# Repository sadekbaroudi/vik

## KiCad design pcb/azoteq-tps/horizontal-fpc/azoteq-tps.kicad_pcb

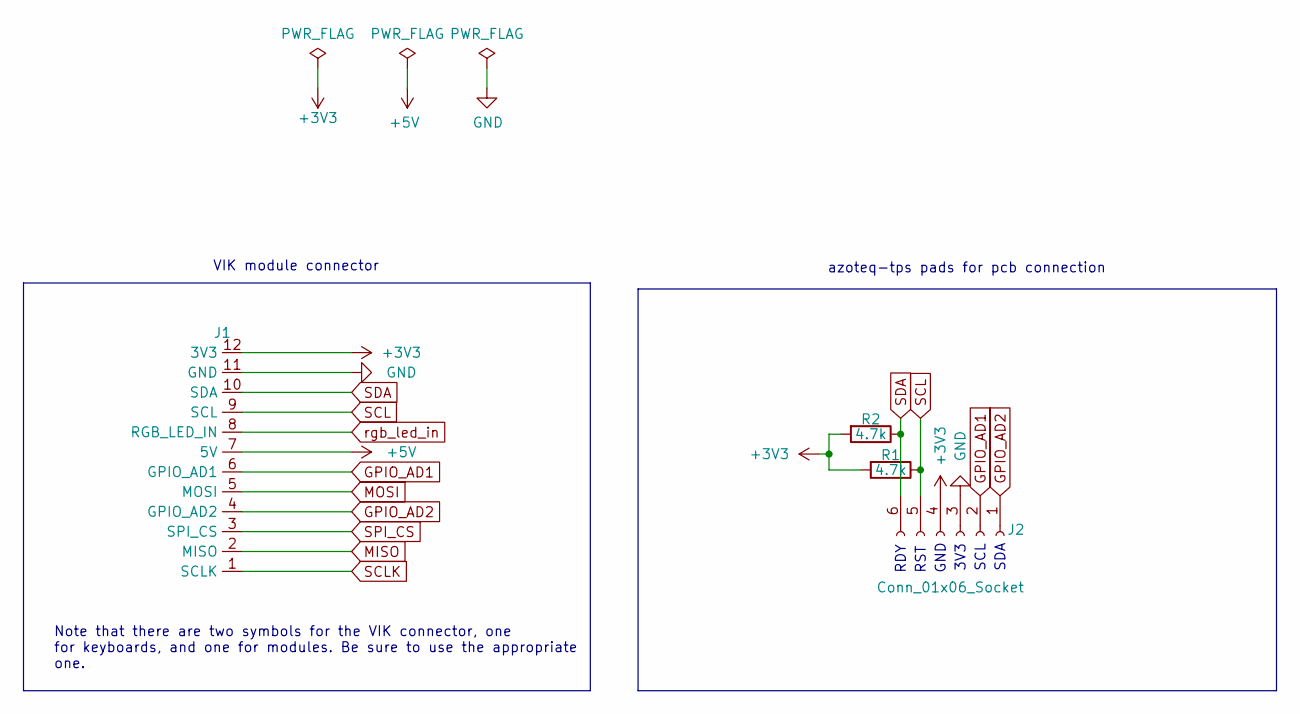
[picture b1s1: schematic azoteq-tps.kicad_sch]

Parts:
J1: vik-module-connector-horizontal-mini; LCSC C2919479
J2: Conn_01x06_Socket; Pad_06_2.00mm
R1, R2: 4.7k; R_0805_2012Metric_Pad1.20x1.40mm_HandSolder; LCSC C115310

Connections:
+3V3: J1.12 (3V3), J2.4, R1.2, R2.2
+5V: J1.7 (5V)
GND: J1.11 (GND), J2.3
GPIO_AD1: J1.6 (GPIO_AD1), J2.2
GPIO_AD2: J1.4 (GPIO_AD2), J2.1
MISO: J1.2 (MISO)
MOSI: J1.5 (MOSI)
SCL: J1.9 (SCL), J2.5, R1.1
SCLK: J1.1 (SCLK)
SDA: J1.10 (SDA), J2.6, R2.1
SPI_CS: J1.3 (SPI_CS)
rgb_led_in: J1.8 (RGB_LED_IN)

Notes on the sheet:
GND
RST
SCL
Note that there are two symbols for the VIK connector, one for keyboards, and one for modules. Be sure to use the appropriate one.
azoteq-tps pads for pcb connection
3V3
SDA
VIK module connector
RDY

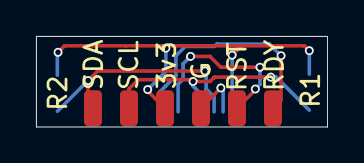
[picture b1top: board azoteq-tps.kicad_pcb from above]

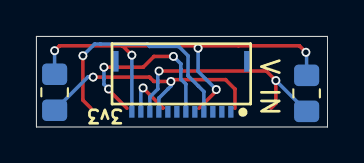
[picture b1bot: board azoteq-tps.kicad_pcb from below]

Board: 2 copper layers, 16.2 x 5.0 mm, 4 parts (3 on the bottom side), 6 nets.

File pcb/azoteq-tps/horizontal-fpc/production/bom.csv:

Designator,Footprint,Quantity,Value,LCSC Part #
J1,vik-module-connector-horizontal-mini,1,~,C2919479
J2,Pad_06_2.00mm,1,Conn_01x06_Socket,
"R1, R2",0805,2,4.7k,C115310

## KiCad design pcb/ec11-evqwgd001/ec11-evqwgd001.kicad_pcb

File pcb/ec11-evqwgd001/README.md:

# ec11 evqwgd001 vik module

## Overview

This is a simple EC11 and EVQWGD001 vik module. It has support for 4 upwards facing SK6812 mini-e leds, in case you want to add a little pizzazz to your encoder.

Please note that this PCB does **not** support the click, only rotation of the encoder.

## Fabrication and BOM

For PCB fabrication, you can use the files in the production folder.

* gerbers.zip - the file used to fabricate the pcb
* bom.csv - used for PCBA. You can also use the part numbers in this file to look up the exact parts as [lcsc.com](https://lcsc.com)
* positions.csv - used for PCBA

Using the 3 files above, this has been tested at [jlcpcb.com](https://jlcpcb.com)

## VIK module certification

| Category                | Classification          | Response           |
| ----------------------- | ----------------------- | ------------------ |
| FPC connector           | Required                | :heavy_check_mark: |
| Breakout pins           | Recommended             | :x:                |
| Uses: SPI               | Optional                | :x:                |
| SPI used for SPI only   | Strongly recommended    | N/A                |
| Uses: I2C               | Optional                | :x:                |
| I2C used for I2C only   | Strongly Recommended    | :x:                |
| I2C pull ups            | Required                | N/A                |
| Uses: RGB               | Optional                | :heavy_check_mark: |
| Uses: Extra GPIO 1      | Optional                | :heavy_check_mark: |
| Uses: Extra GPIO 2      | Optional                | :heavy_check_mark: |
| Standard PCB Size/Mount | Strongly recommended    | :x:                |

## PCB images

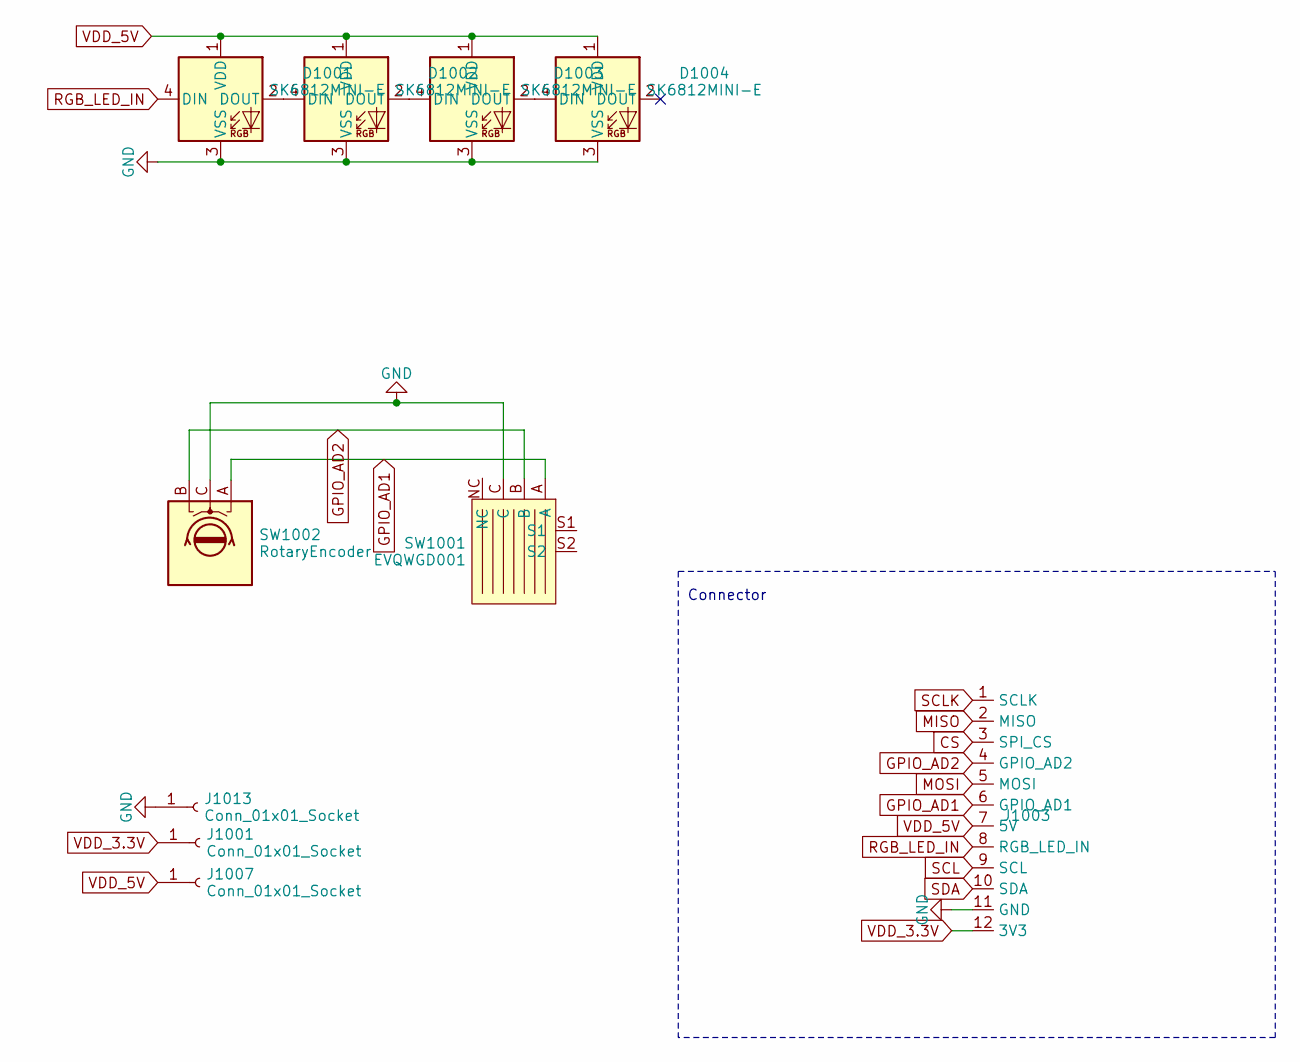
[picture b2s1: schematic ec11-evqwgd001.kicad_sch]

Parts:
D1001, D1002, D1003, D1004: SK6812MINI-E; SK6812MINI-E-no-switch-outline
J1001, J1007, J1013: Conn_01x01_Socket; SolderWire-0.5sqmm_1x01_D0.9mm_OD2.3mm
J1003: vik-module-connector-horizontal; LCSC C2919557
SW1001: EVQWGD001
SW1002: RotaryEncoder; RotaryEncoder_EC11-no-legs

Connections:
CS: J1003.3 (SPI_CS)
GND: D1001.3 (VSS), D1002.3 (VSS), D1003.3 (VSS), D1004.3 (VSS), J1003.11 (GND), J1013.1, SW1001.C, SW1002.C
GPIO_AD1: J1003.6 (GPIO_AD1), SW1001.A, SW1002.A
GPIO_AD2: J1003.4 (GPIO_AD2), SW1001.B, SW1002.B
MISO: J1003.2 (MISO)
MOSI: J1003.5 (MOSI)
unnamed: D1001.2 (DOUT), D1002.4 (DIN)
unnamed: D1002.2 (DOUT), D1003.4 (DIN)
unnamed: D1003.2 (DOUT), D1004.4 (DIN)
RGB_LED_IN: D1001.4 (DIN), J1003.8 (RGB_LED_IN)
SCL: J1003.9 (SCL)
SCLK: J1003.1 (SCLK)
SDA: J1003.10 (SDA)
VDD_3.3V: J1001.1, J1003.12 (3V3)
VDD_5V: D1001.1 (VDD), D1002.1 (VDD), D1003.1 (VDD), D1004.1 (VDD), J1003.7 (5V), J1007.1

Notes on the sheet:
Connector

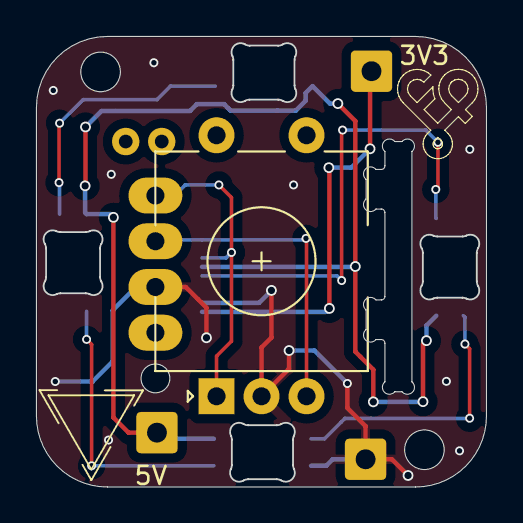
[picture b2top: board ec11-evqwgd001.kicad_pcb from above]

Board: 2 copper layers, 25.0 x 25.0 mm, 10 parts (1 on the bottom side), 9 nets.

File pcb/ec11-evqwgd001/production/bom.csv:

Designator,Footprint,Quantity,Value,LCSC Part #
"_2, ",,2,,
"D1001, D1002, D1003, D1004",SK6812MINI-E-no-switch-outline,4,SK6812MINI-E,
"J1001, J1007, J1013",SolderWire-0.5sqmm_1x01_D0.9mm_OD2.3mm,3,Conn_01x01_Socket,
J1003,vik-module-connector-horizontal,1,~,C2919557
SW1001,EVQWGD001,1,EVQWGD001,
SW1002,RotaryEncoder_EC11-no-legs,1,RotaryEncoder,

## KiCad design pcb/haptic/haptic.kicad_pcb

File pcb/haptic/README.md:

# Haptic feedback module

## Overview

This is a VIK module made to house the [Pimoroni DRV2605L](https://shop.pimoroni.com/products/drv2605l-linear-actuator-haptic-breakout?variant=27859486867539) breakout board.

## Fabrication and BOM

For PCB fabrication, you can use the files in the production folder.

* gerbers.zip - the file used to fabricate the pcb
* bom.csv - used for PCBA. You can also use the part numbers in this file to look up the exact parts as [lcsc.com](https://lcsc.com)
* positions.csv - used for PCBA

Using the 3 files above, this has been tested at [jlcpcb.com](https://jlcpcb.com)

## VIK module certification

| Category                | Classification          | Response           |
| ----------------------- | ----------------------- | ------------------ |
| FPC connector           | Required                | :heavy_check_mark: |
| Breakout pins           | Recommended             | :x:                |
| Uses: SPI               | Optional                | :x:                |
| SPI used for SPI only   | Strongly recommended    | N/A                |
| Uses: I2C               | Optional                | :heavy_check_mark: |
| I2C used for I2C only   | Strongly Recommended    | :heavy_check_mark: |
| I2C pull ups            | Required                | 4.7kΩ              |
| Uses: RGB               | Optional                | :x:                |
| Uses: Extra GPIO 1      | Optional                | :x:                |
| Uses: Extra GPIO 2      | Optional                | :x:                |
| Standard PCB Size/Mount | Strongly recommended    | :x:                |

## PCB images

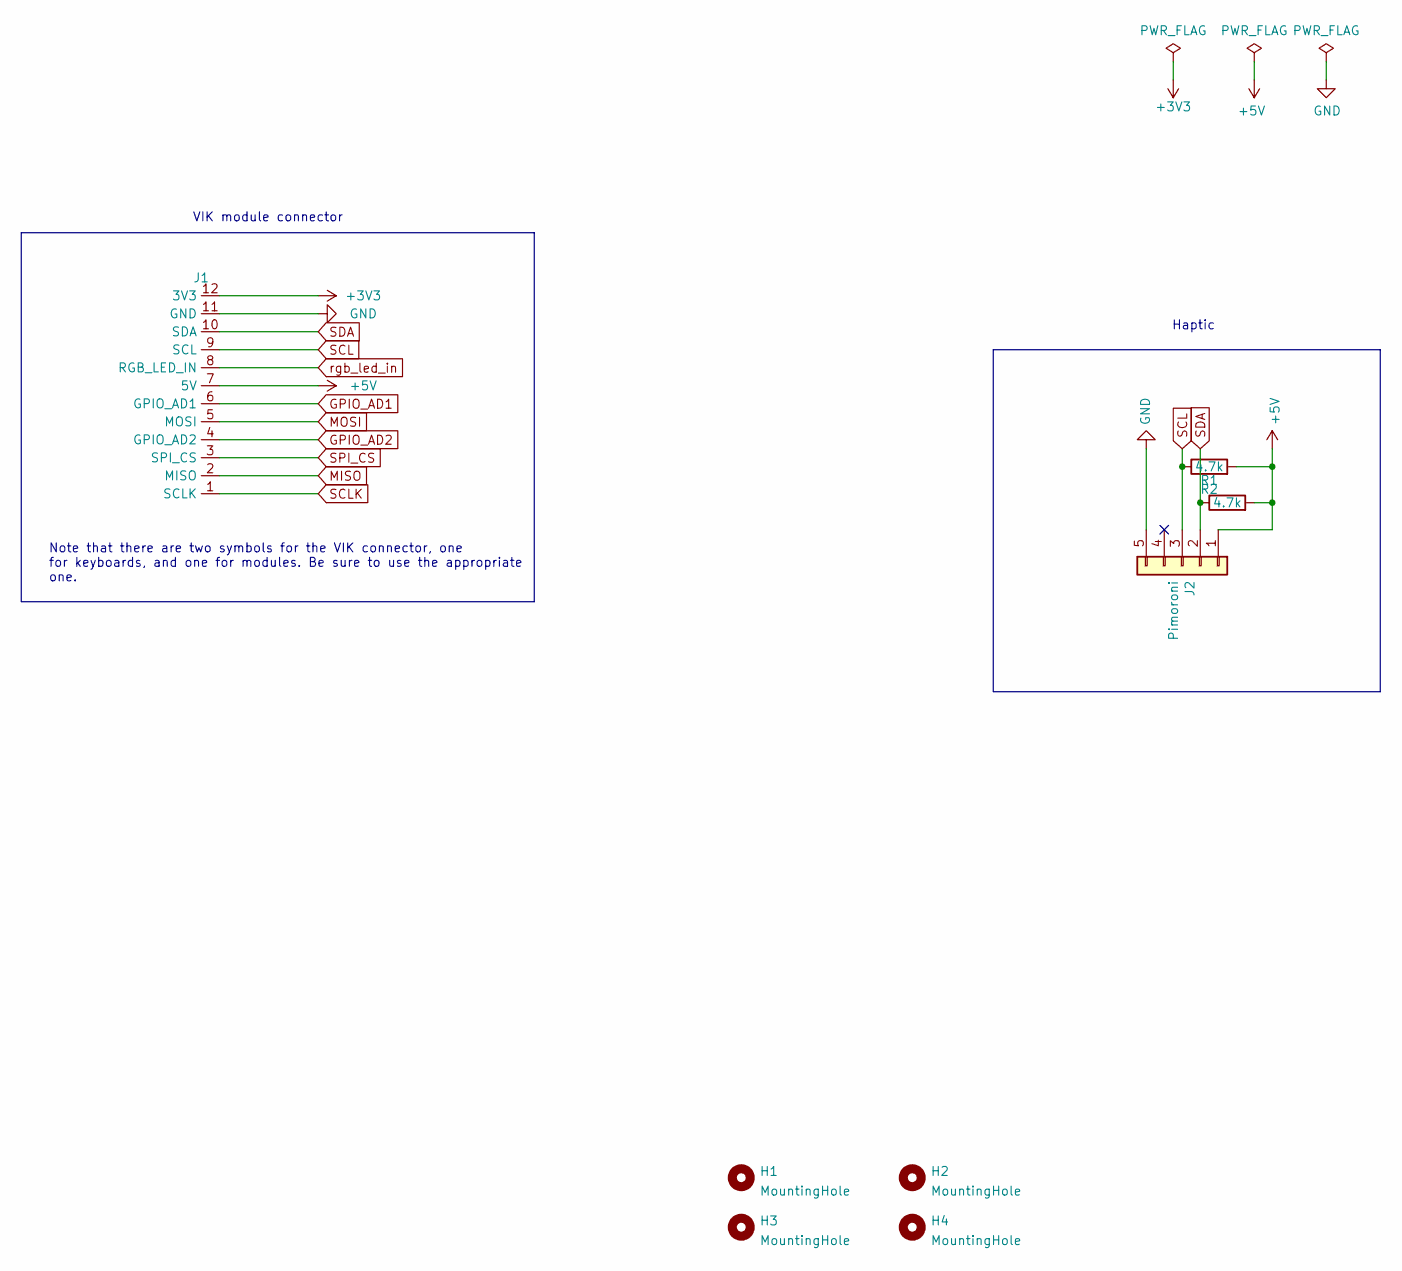
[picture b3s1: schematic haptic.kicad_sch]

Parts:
H1, H2, H3, H4: MountingHole; MountingHole_2.2mm_M2_DIN965_Pad
J1: vik-module-connector-horizontal; LCSC C479750
J2: Pimoroni; Pimoroni Haptic Buzz DRV2605L Driver
R1, R2: 4.7k; D3_TH_SMD; LCSC C104821

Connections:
+3V3: J1.12 (3V3)
+5V: J1.7 (5V), J2.1, R1.2, R2.2
GND: J1.11 (GND), J2.5
GPIO_AD1: J1.6 (GPIO_AD1)
GPIO_AD2: J1.4 (GPIO_AD2)
MISO: J1.2 (MISO)
MOSI: J1.5 (MOSI)
SCL: J1.9 (SCL), J2.3, R1.1
SCLK: J1.1 (SCLK)
SDA: J1.10 (SDA), J2.2, R2.1
SPI_CS: J1.3 (SPI_CS)
rgb_led_in: J1.8 (RGB_LED_IN)

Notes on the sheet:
Note that there are two symbols for the VIK connector, one for keyboards, and one for modules. Be sure to use the appropriate one.
VIK module connector
Haptic

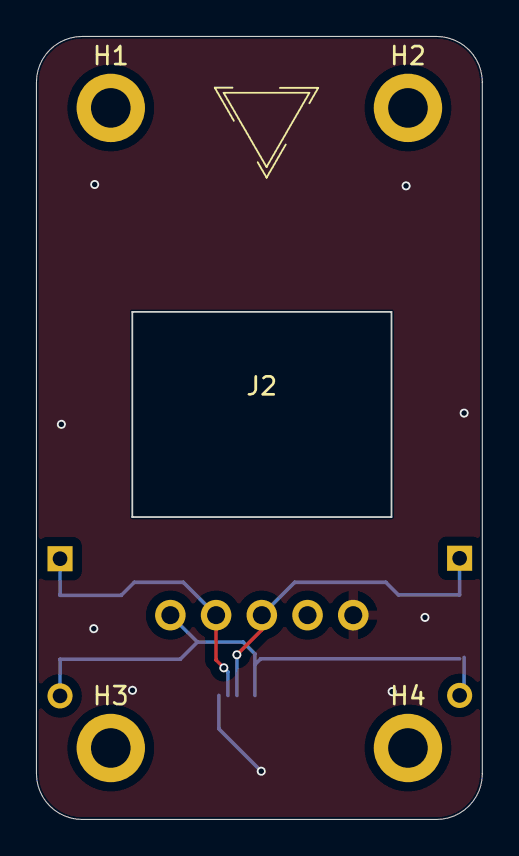
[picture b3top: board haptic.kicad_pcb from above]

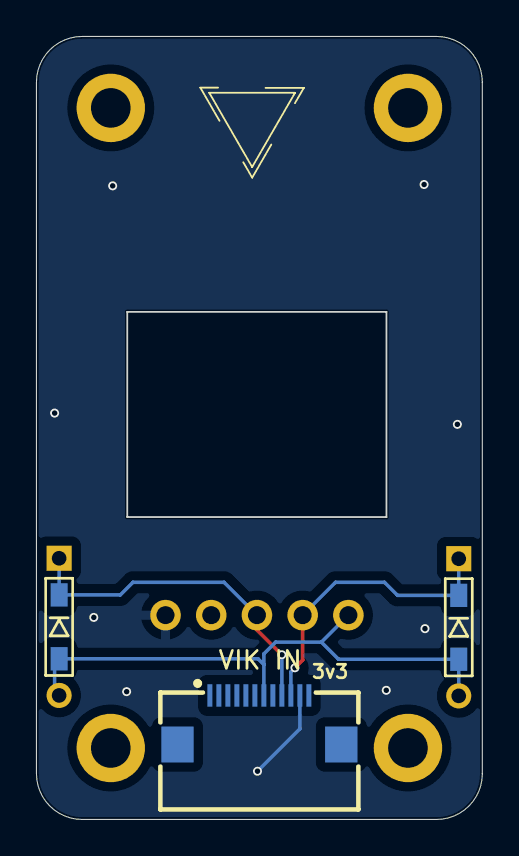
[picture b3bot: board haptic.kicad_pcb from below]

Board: 2 copper layers, 24.8 x 43.5 mm, 8 parts (3 on the bottom side), 4 nets.

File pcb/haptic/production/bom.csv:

Designator,Footprint,Quantity,Value,LCSC Part #
"H1, H2, H3, H4",MountingHole_2.2mm_M2_DIN965_Pad,4,MountingHole,
J1,vik-module-connector-horizontal,1,~,C479750
J2,Pimoroni Haptic Buzz DRV2605L Driver,1,Pimoroni,
"R1, R2",D3_TH_SMD,2,4.7k,C104821

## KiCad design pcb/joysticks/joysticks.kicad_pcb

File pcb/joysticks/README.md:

# joysticks vik module

## Overview

This is a vik module to support the following joysticks:  
* [adafruit 2765](https://www.adafruit.com/product/2765)
* [sparkfun 9032](https://www.sparkfun.com/products/9032)
* [nintendo joycon joystick](https://www.amazon.com/Replacement-Joystick-Nintendo-Original-Professional/dp/B08397JQZG/)

Please note that this PCB does **not** support the click on the sparkfun analog joystick, only x and y movements

## Fabrication and BOM

For PCB fabrication, you can use the files in the production folder.

* gerbers.zip - the file used to fabricate the pcb
* bom.csv - used for PCBA. You can also use the part numbers in this file to look up the exact parts as [lcsc.com](https://lcsc.com)
* positions.csv - used for PCBA

Using the 3 files above, this has been tested at [jlcpcb.com](https://jlcpcb.com)

## VIK module certification

| Category                | Classification          | Response           |
| ----------------------- | ----------------------- | ------------------ |
| FPC connector           | Required                | :heavy_check_mark: |
| Breakout pins           | Recommended             | :x:                |
| Uses: SPI               | Optional                | :x:                |
| SPI used for SPI only   | Strongly recommended    | N/A                |
| Uses: I2C               | Optional                | :x:                |
| I2C used for I2C only   | Strongly Recommended    | :x:                |
| I2C pull ups            | Required                | N/A                |
| Uses: RGB               | Optional                | :x:                |
| Uses: Extra GPIO 1      | Optional                | :heavy_check_mark: |
| Uses: Extra GPIO 2      | Optional                | :heavy_check_mark: |
| Standard PCB Size/Mount | Strongly recommended    | :x:                |

## PCB images

## joycon joystick wiring

Caution: I have not tested the joycon joystick, but I wired per the image below  

I got this diagram from here:  
https://sudomod.com/forum/viewtopic.php?t=3485

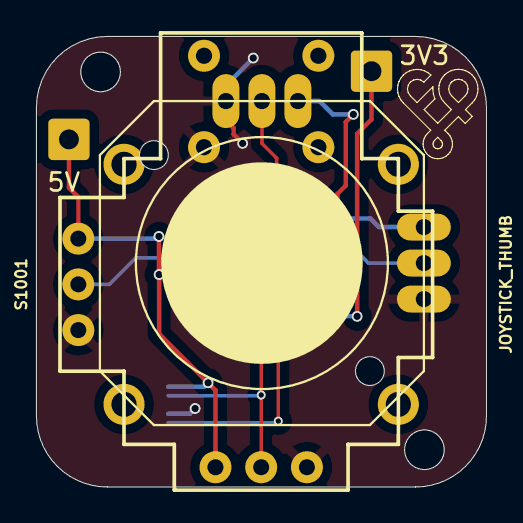
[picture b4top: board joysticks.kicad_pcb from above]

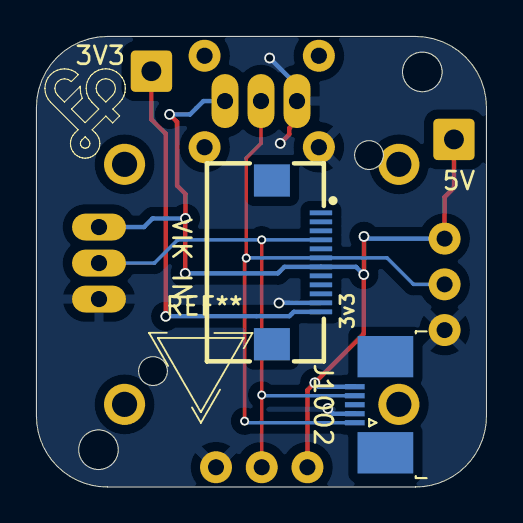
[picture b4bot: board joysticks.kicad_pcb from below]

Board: 2 copper layers, 25.0 x 25.0 mm, 6 parts (2 on the bottom side), 5 nets.

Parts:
J1001, J1007: Conn_01x01_Socket; SolderWire-0.5sqmm_1x01_D0.9mm_OD2.3mm
J1002: Conn_01x05_Socket; TE_0-1734839-5_1x05-1MP_P0.5mm_Horizontal
J1003: vik-module-connector-horizontal
JOY1001: JOYSTICK_ANALOG_XY; joystick_analog_xy
S1001: JOYSTICK_THUMB; sparkfun_9032_joystick_thumb

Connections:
GND: J1002.2, J1003.11 (GND), JOY1001.X- (A), JOY1001.Y- (A), S1001.B2A (SEL-), S1001.H3 (H-), S1001.V3 (V-)
GPIO_AD1: J1002.1, J1003.6 (GPIO_AD1), JOY1001.X (S), S1001.V2 (V)
GPIO_AD2: J1002.4, J1003.4 (GPIO_AD2), JOY1001.Y (S), S1001.H2 (H)
VDD_3.3V: J1001.1, J1003.12 (3V3)
VDD_5V: J1002.5, J1003.7 (5V), J1007.1, JOY1001.X+ (E), JOY1001.Y+ (E), S1001.H1 (H+), S1001.V1 (V+)

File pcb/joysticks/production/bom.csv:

Designator,Footprint,Quantity,Value,LCSC Part #
"_2, ",,2,,
"J1001, J1007",SolderWire-0.5sqmm_1x01_D0.9mm_OD2.3mm,2,Conn_01x01_Socket,
J1002,TE_0-1734839-5_1x05-1MP_P0.5mm_Horizontal,1,Conn_01x05_Socket,C3041165
J1003,vik-module-connector-horizontal,1,~,C2919557
JOY1001,joystick_analog_xy,1,JOYSTICK_ANALOG_XY,
S1001,sparkfun_9032_joystick_thumb,1,JOYSTICK_THUMB,

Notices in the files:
pcb/ec11-evqwgd001/ec11-evqwgd001.kicad_sch:
Copyright Quentin Lebastard
